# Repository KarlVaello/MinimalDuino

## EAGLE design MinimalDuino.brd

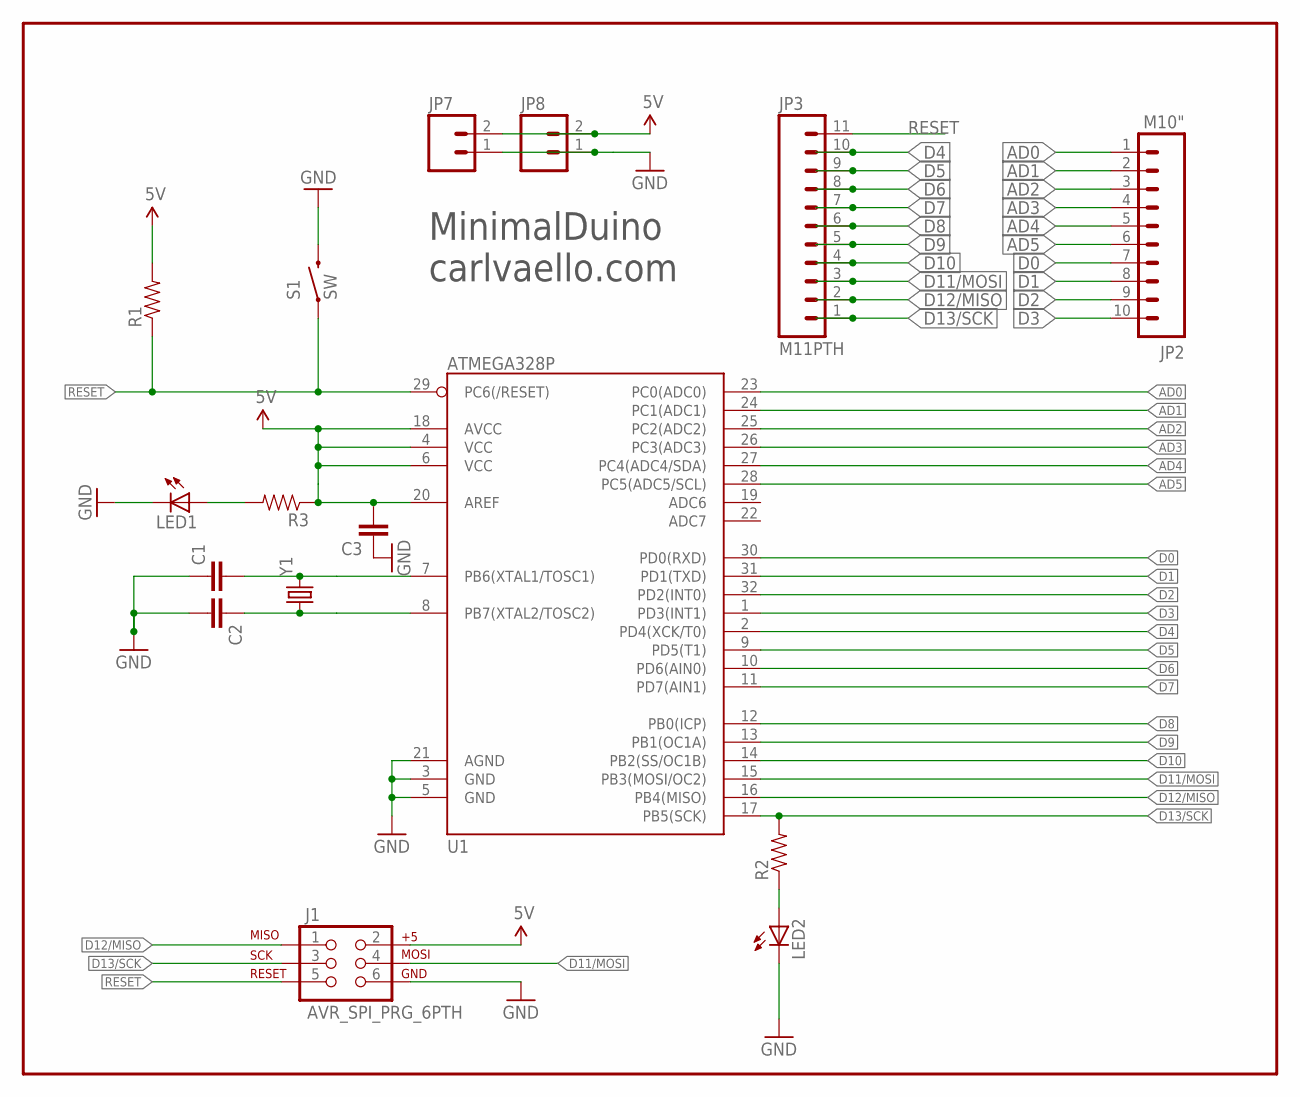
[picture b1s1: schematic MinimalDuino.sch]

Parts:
C1, C2, C3: CAP0805; 0805
J1: AVR_SPI_PRG_6PTH; 2X3
JP2: M10"; 1X10
JP3: M11PTH; 1X11
JP7, JP8: M02PTH; 1X02
LED1, LED2: LEDSML0805; SML0805
R1, R2, R3: RESISTOR0805-RES; 0805
S1: SW; TACTILE-PTH-SIDEEZ
U1: ATMEGA328P; TQFP32-08
Y1: CRYSTALHC49US; HC49US

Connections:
5V: C3.2, J1.2, JP7.2, JP8.2, R1.2, R3.1, U1.4 (VCC), U1.6 (VCC), U1.18 (AVCC), U1.20 (AREF)
AD0: JP2.1, U1.23 (PC0(ADC0))
AD1: JP2.2, U1.24 (PC1(ADC1))
AD2: JP2.3, U1.25 (PC2(ADC2))
AD3: JP2.4, U1.26 (PC3(ADC3))
AD4: JP2.5, U1.27 (PC4(ADC4/SDA))
AD5: JP2.6, U1.28 (PC5(ADC5/SCL))
D0: JP2.7, U1.30 (PD0(RXD))
D1: JP2.8, U1.31 (PD1(TXD))
D2: JP2.9, U1.32 (PD2(INT0))
D3: JP2.10, U1.1 (PD3(INT1))
D4: JP3.10, U1.2 (PD4(XCK/T0))
D5: JP3.9, U1.9 (PD5(T1))
D6: JP3.8, U1.10 (PD6(AIN0))
D7: JP3.7, U1.11 (PD7(AIN1))
D8: JP3.6, U1.12 (PB0(ICP))
D9: JP3.5, U1.13 (PB1(OC1A))
D10: JP3.4, U1.14 (PB2(SS/OC1B))
D11/MOSI: J1.4, JP3.3, U1.15 (PB3(MOSI/OC2))
D12/MISO: J1.1, JP3.2, U1.16 (PB4(MISO))
D13/SCK: J1.3, JP3.1, R2.2, U1.17 (PB5(SCK))
GND: C1.1, C2.2, C3.1, J1.6, JP7.1, JP8.1, LED1.C, LED2.C, S1.2, U1.3 (GND), U1.5 (GND), U1.21 (AGND)
unnamed: C1.2, U1.7 (PB6(XTAL1/TOSC1)), Y1.2
unnamed: C2.1, U1.8 (PB7(XTAL2/TOSC2)), Y1.1
unnamed: LED1.A, R3.2
unnamed: LED2.A, R2.1
RESET: J1.5, JP3.11, R1.1, S1.1, U1.29 (PC6(/RESET))

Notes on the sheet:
MinimalDuino carlvaello.com

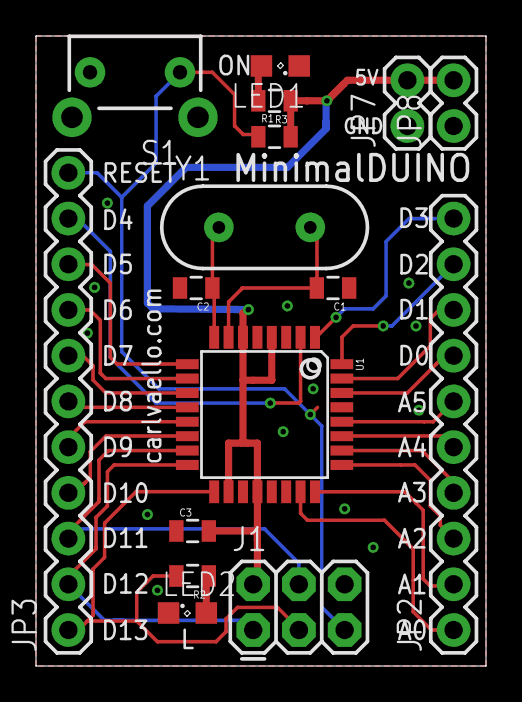
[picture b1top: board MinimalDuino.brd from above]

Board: 4 copper layers, 25.0 x 35.0 mm, 16 parts (0 on the bottom side), 27 nets.

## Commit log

2016-11-10 :neckbeard: Added .gitattributes
2016-11-10 Initial Commit
    Initial Commit - MinimalDuino
2016-11-10 Board update
    Board update
2016-11-13 Added License file
    Added License.txt
2016-11-14 Board and schematic updates
    Board and schematic updates

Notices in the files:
parts and their libraries:
SparkFun-DigitalIC: Licensing: CC v3.0 Share-Alike You are welcome to use this library for commercial purposes.
